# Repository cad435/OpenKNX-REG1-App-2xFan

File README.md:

# REG1-FanAktor-2x (V0.2)

Applikationsplatine (Addon-Board) für das [OpenKNX REG1](https://github.com/OpenKNX/OpenKNX-REG1) Modulsystem zur Ansteuerung von bis zu zwei Lüftern.

## Überblick

Die REG1-FanAktor-2x Platine wird zusammen mit dem [REG1-Controller2040](https://github.com/OpenKNX/OpenKNX-REG1/tree/main/hardware/EDA-Files/REG1-Controller2040) (RP2040-basiert) als Applikationsplatine in einem [REG1-Gehäuse](https://github.com/OpenKNX/OpenKNX/wiki/REG1-Case) (1TE, 17.5mm, DIN-Hutschiene) verbaut.

Die Platine steuert bis zu **2 unabhängige Lüfterausgänge** (Kanal A und B), jeweils mit:
- **PWM-Drehzahlregelung** (Open-Drain, 3.3V -> 5V über Level-Shifter)
- **Leistungsschalter** (High-Side-Switch für Ein/Aus)
- **Tacho-Eingang** (galvanisch isoliert über Optokoppler)

## Anschlüsse

### Lüfterklemmen

| Klemme | Bezeichnung | Funktion |
|--------|-------------|----------|
| **P1** | PWR IN | Lüfter-Versorgungsspannung (12...24V DC), 2-polig (FAN+, GND_FAN) |
| **P2** | FAN A | Lüfterausgang Kanal A, 4-polig (PWM_A_OUT, Tacho_A_IN, GND_FAN, GND_FAN) |
| **P3** | FAN B | Lüfterausgang Kanal B, 4-polig (PWM_B_OUT, Tacho_B_IN, GND_FAN, GND_FAN) |

Klemmentyp: KF2EDGR-3.5 (P1: 2-polig, P2/P3: 4-polig), Rastermaß 3.5mm.

### Controller-Schnittstelle

| Anschluss | Funktion |
|-----------|----------|
| **J1** | Header 1x10, Verbindung zum REG1-Controller2040 (GPIO, Versorgung) |

#### J1 Pinbelegung (vom Controller)

| Pin | Signal | GPIO | Funktion |
|-----|--------|------|----------|
| 1 | 12V | -- | Versorgungsspannung vom Controller |
| 2 | 3V3 | -- | 3.3V Versorgung vom Controller |
| 3 | GND_KNX | -- | Masse |
| 4 | GPIO18 | GP18 | PWM Kanal A |
| 5 | GPIO27 | GP27 | Tacho Kanal A (Eingang) |
| 6 | GPIO28 | GP28 | PWM Kanal B |
| 7 | GPIO29 | GP29 | Power-Switch Kanal A |
| 8 | GPIO26 | GP26 | Power-Switch Kanal B |
| 9 | GPIO17 | GP17 | Tacho Kanal B (Eingang) |
| 10 | GPIO16 | GP16 | Spare (auf J1 herausgeführt, nicht belegt) |

## Schaltungsbeschreibung

### Spannungsversorgung

Die Lüfter werden extern mit 12...24V DC über P1 versorgt.

### PWM-Ausgänge (Kanal A/B)

Jeder Kanal hat einen PWM-Ausgang zur Drehzahlregelung der Lüfter. Die Ausgänge sind galvanisch vom KNX-Bus getrennt ausgeführt.

### PWM Pull-Up Konfiguration (CN1...CN6)

Die Pull-Up-Konfiguration für die *PWM-Steuerung* wird über Lötbrücken eingestellt:

| Lüfter-Typ | Kanal A | Kanal B | Beschreibung |
|-------------|---------|---------|-------------|
| Interner Pull-Up vorhanden | Keine Brücke | Keine Brücke | Standardlüfter, keine externe Beschaltung nötig |
| Pull-Up auf 5V nötig | CN2 brücken | CN5 brücken | Pull-Up auf 5V |
| Pull-Up auf VCC (12-24V) nötig | CN1 brücken | CN4 brücken | Pull-Up auf Versorgungsspannung |
| Push-Pull Eingang | CN3 brücken, R1 entfernen | CN6 brücken, R3 entfernen | Für Lüfter mit Push-Pull-PWM-Eingang |

### ⚠️⚠️ Hinweis: ⚠️⚠️

Standard PC Lüfter und frei verkäufliche Typen haben zu 99% einen Integrierten Pullup. Standardmäßig ist keine der CNx Lötbrücken gesetzt, sodass diese Lüfter "out-of-the-box" funktionieren.

Bei Integrierten Anlagen (zum Beispiel dezentralen Lüftersystemen in der Gebäudetechnik) werden auch mal OEM-Varianten OHNE integrierte Pullups verbaut. Es empfiehlt sich ein genauer Blick auf die exakte Typennummer! Oftmals ist nur der Suffix ein Hinweis darauf. 

Von diesen Lüftern findet man in der Regel auch kein frei verfügbares Datenblatt. Hier muss man etwas Googlen welches die spezifische Referenzsspannung des jeweiligen Lüfterherstellers ist (bei ebm-Papst zum Beispiel meistens (!) 5V). Bei anderen Herstellern sind hier ggf. mit 3.3V oder anderem zu rechnen.

Eine Haftung für Schäden ist ausgeschlossen!

### Tacho-Eingänge

Jeder Kanal hat einen galvanisch getrennten Tacho-Eingang.

Typische Lüfter liefern 2 Pulse pro Umdrehung.

### Leistungsschalter (Power Ein/Aus)

Jeder Kanal hat einen High-Side-Switch zum An- und Ausschalten der Supply-Spannung für den Lüfter. Dies dient rein zur Eliminierung der Standbyleistung.

## Firmware

Die zugehörige Firmware basiert auf dem [OpenKNX](https://github.com/OpenKNX) Framework. Diese
Platine ist die **Referenz-Hardware** der Applikation — sie wird dort als primäre Variante
geführt und ist die einzige mit Tacho-Eingang:

- **OAM-FanControl**: [github.com/OpenKNX/OAM-FanControl](https://github.com/OpenKNX/OAM-FanControl/tree/cad435/main) (Branch `cad435/main`)
- **OFM-FanControl**: [github.com/OpenKNX/OFM-FanControl](https://github.com/OpenKNX/OFM-FanControl/tree/cad435/main) (Branch `cad435/main`)

Entwickelt wird in den Forks [cad435/OAM-FanControl](https://github.com/cad435/OAM-FanControl) und
[cad435/OFM-FanControl](https://github.com/cad435/OFM-FanControl) (Branch `main`).

Die Boardauswahl erfolgt zur Compile-Zeit, weil sich PWM-Polarität und Anzahl der Ausgänge
zwischen den Varianten unterscheiden. Für diese Platine ist das Environment
`develop_RP2040` zuständig.

> **Herkunft:** Ursprung der Applikation sind
> [mrspieb/OAM-FanControl](https://github.com/mrspieb/OAM-FanControl) und
> [mrspieb/OFM-FanControl](https://github.com/mrspieb/OFM-FanControl) für die
> [HW-FanControl](https://github.com/mrspieb/HW-FanController)-Platine. Die oben genannten
> Repositories sind Forks davon und inzwischen neu aufgebaut: Master/Slave-Gruppenbetrieb,
> reversierende Lüfter mit bipolarer Stellgröße auf einem Ausgang, Volumenstromkennlinie,
> Blockiererkennung. Das KO-Layout ist dadurch **nicht** mit der ursprünglichen Applikation
> kompatibel.

## Dateien

| Datei | Beschreibung |
|-------|-------------|
| `REG1-FanAktor-2x_V0.2-Schematic.PDF` | Schaltplan |
| `REG1-FanAktor-2x_V0.2-Pinout.PDF` | Pinbelegung und Lötbrücken-Konfiguration |
| `REG1-FanAktor-2x_V0.2_Assembly.PDF` | Bestückungsplan (Top/Bottom) |
| `BOM-REG1-FanAktor-2x(V0.2).pdf` | Stückliste |
| `JLC_PCBA_BOM-REG1-FanAktor-2x(V0.2).xlsx` | BOM für JLCPCB-Bestückung |
| `JLC_PCBA_CPL-REG1-FanAktor-2x(V0.2).xlsx` | Bauteilplatzierung für JLCPCB |
| `REG1-FanAktor-2x_Gerber.zip` | Gerber-Daten für PCB-Fertigung |
| `REG1-FanAktor-2x(V0.2).step` | 3D-Modell |

## Lizenz

Dieses Projekt ist Teil des [OpenKNX](https://github.com/OpenKNX) Ökosystems.

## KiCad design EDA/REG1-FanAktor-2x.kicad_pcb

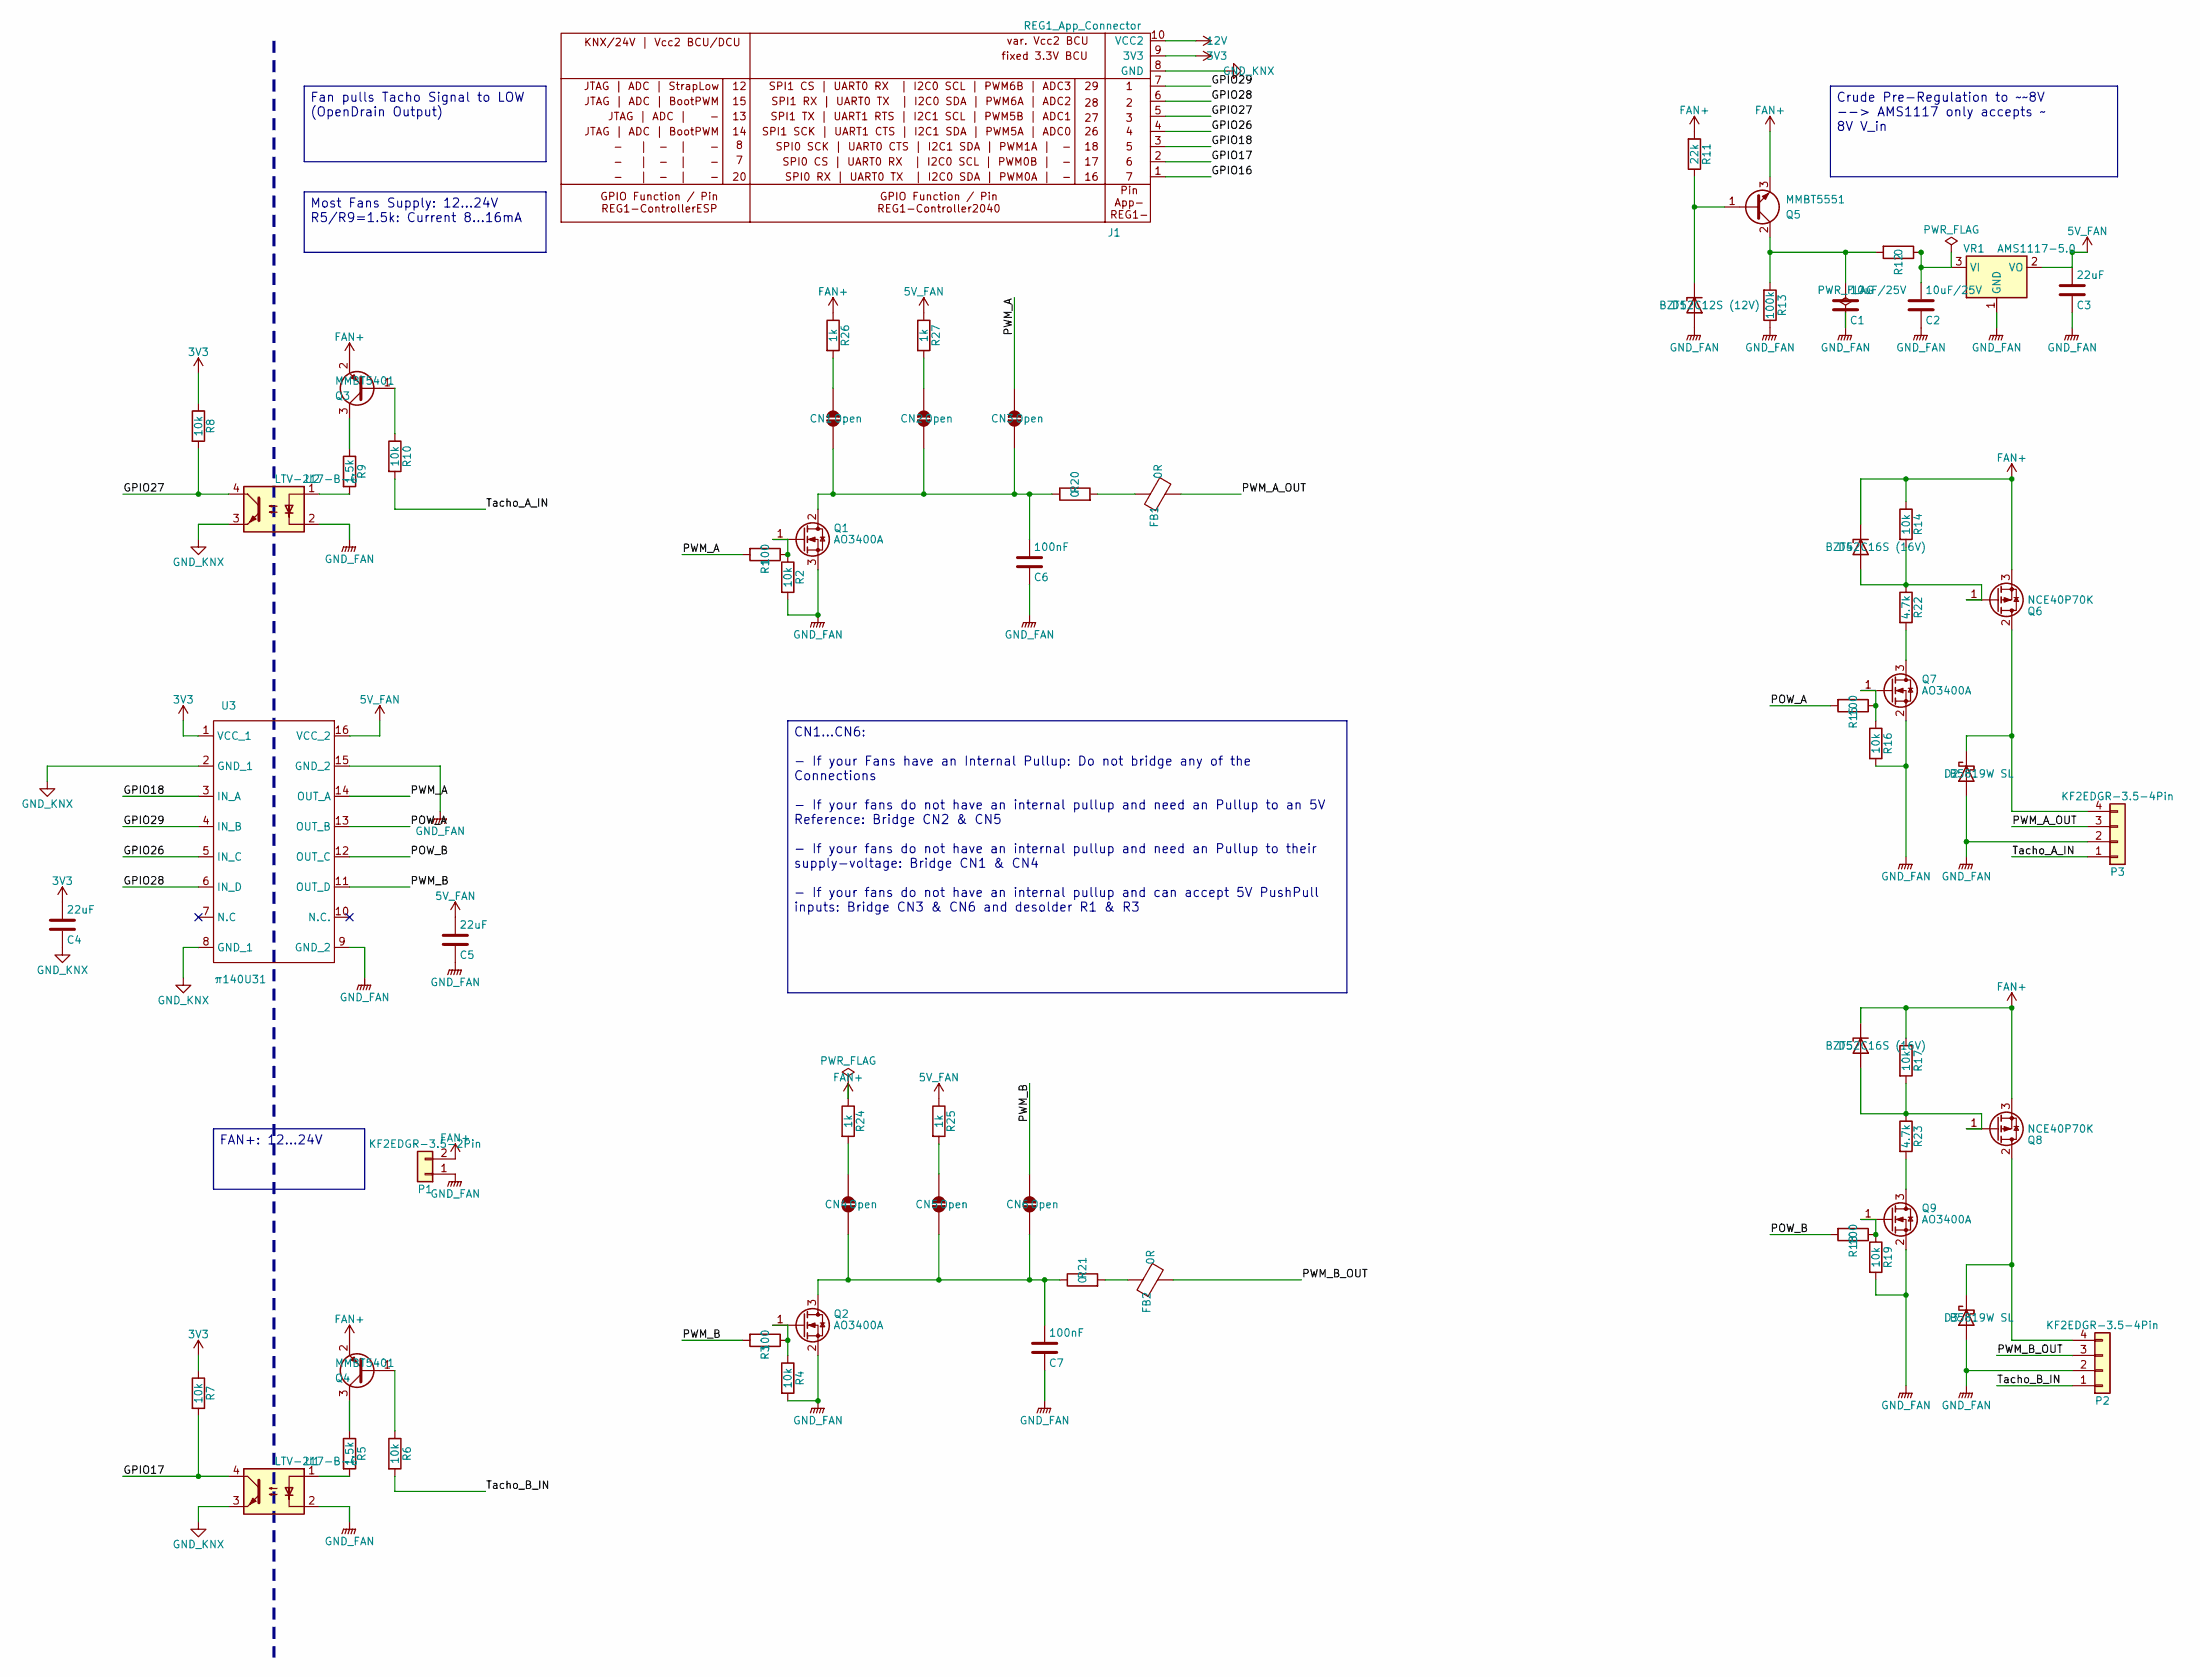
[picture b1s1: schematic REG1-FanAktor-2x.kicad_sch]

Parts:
C1, C2: 10uF/25V; C_0805_2012Metric; LCSC C440198
C3, C4, C5: 22uF; C_0805_2012Metric; LCSC C45783
C6, C7: 100nF; C_0603_1608Metric
CN1, CN2, CN3, CN4, CN5, CN6: Open; SB_0603
D1: BZT52C12S (12V); D_SOD-323; LCSC C19077447
D2, D3: B5819W SL; D_SOD-123; LCSC C8598
D4, D5: BZT52C16S (16V); D_SOD-323; LCSC C19077449
FB1, FB2: 0R; L_1206_3216Metric; LCSC C17888
J1: REG1_App_Connector; PinHeader_1x10_P2.54mm_Vertical
P1: KF2EDGR-3.5-2Pin; CONN-TH_2P-P3.50_KF2EDGR-3.5; LCSC C441171
P2, P3: KF2EDGR-3.5-4Pin; CONN-TH_4P-P3.50_KF2EDGR-3.5-4P
Q1: AO3400A; SOT23_Normal; LCSC C20917
Q2, Q7, Q9: AO3400A; SOT-23; LCSC C20917
Q3: MMBT5401; SOT-23; LCSC C8326
Q4: MMBT5401; SOT23_Reverse; LCSC C8326
Q5: MMBT5551; SOT-23; LCSC C2145
Q6, Q8: NCE40P70K; TO-252-2; LCSC C130101
R1, R3, R15, R18: 100; R_0603_1608Metric; LCSC C22775
R2, R4, R6, R7, R8, R10, R14, R16, R17, R19: 10k; R_0603_1608Metric; LCSC C25804
R5, R9: 1.5k; R_0603_1608Metric; LCSC C22843
R11: 22k; R_0603_1608Metric; LCSC C31850
R12, R20, R21: 0; R_1206_3216Metric; LCSC C17888
R13: 100k; R_0603_1608Metric; LCSC C25803
R22, R23: 4.7k; R_1206_3216Metric; LCSC C17936
R24, R25, R26: 1k; R_0805_2012Metric; LCSC C17513
R27: 1k; R0805; LCSC C17513
U1, U2: LTV-217-B-G; SOP-4_4.4x2.6mm_P1.27mm; LCSC C115450
U3: π140U31; SOIC127P600X180-16N; LCSC C471601
VR1: AMS1117-5.0; SOT-223-3_TabPin2; LCSC C6187

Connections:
3V3: C4.2, J1.9 (3V3), R7.1, R8.1, U3.1 (VCC_1)
5V_FAN: C3.2, C5.2, R25.1, R27.1, U3.16 (VCC_2), VR1.2 (VO)
12V: J1.10 (VCC2)
/GPIO16: J1.1
/GPIO17: J1.2, R7.2, U1.4
/GPIO18: J1.3, U3.3 (IN_A)
/GPIO26: J1.4, U3.5 (IN_C)
/GPIO27: J1.5, R8.2, U2.4
/GPIO28: J1.6, U3.6 (IN_D)
/GPIO29: J1.7, U3.4 (IN_B)
/POW_A: R15.2, U3.13 (OUT_B)
/POW_B: R18.2, U3.12 (OUT_C)
/PWM_A: CN3.2 (B), R1.2, U3.14 (OUT_A)
/PWM_A_OUT: FB1.2, P3.3
/PWM_B: CN6.2 (B), R3.2, U3.11 (OUT_D)
/PWM_B_OUT: FB2.2, P2.3
/Tacho_A_IN: P3.1, R10.2
/Tacho_B_IN: P2.1, R6.2
FAN+: D4.1 (K), D5.1 (K), P1.2, Q3.2 (E), Q4.2 (E), Q5.3 (E), Q6.3 (S), Q8.3 (S), R11.2, R14.1, R17.1, R24.1, R26.1
GND_FAN: C1.1, C2.1, C3.1, C5.1, C6.1, C7.1, D1.2 (A), D2.2 (A), D3.2 (A), P1.1, P2.2, P3.2, Q1.3 (S), Q2.2 (S), Q7.2 (S), Q9.2 (S), R2.2, R4.2, R13.1, R16.2, R19.2, U1.2, U2.2, U3.9 (GND_2), U3.15 (GND_2), VR1.1 (GND)
GND_KNX: C4.1, J1.8 (GND), U1.3, U2.3, U3.2 (GND_1), U3.8 (GND_1)
unnamed: C6.2, CN1.1 (A), CN2.1 (A), CN3.1 (A), Q1.2 (D), R20.1
unnamed: CN1.2 (B), R26.2
unnamed: CN2.2 (B), R27.2
unnamed: C7.2, CN4.1 (A), CN5.1 (A), CN6.1 (A), Q2.3 (D), R21.1
unnamed: CN4.2 (B), R24.2
unnamed: CN5.2 (B), R25.2
unnamed: D1.1 (K), Q5.1 (B), R11.1
unnamed: D2.1 (K), P3.4, Q6.2 (D)
unnamed: D3.1 (K), P2.4, Q8.2 (D)
unnamed: D4.2 (A), Q6.1 (G), R14.2, R22.1
unnamed: D5.2 (A), Q8.1 (G), R17.2, R23.1
unnamed: FB1.1, R20.2
unnamed: FB2.1, R21.2
unnamed: Q1.1 (G), R1.1, R2.1
unnamed: Q2.1 (G), R3.1, R4.1
unnamed: Q3.1 (B), R10.1
unnamed: Q3.3 (C), R9.1
unnamed: Q4.1 (B), R6.1
unnamed: Q4.3 (C), R5.1
unnamed: C1.2, Q5.2 (C), R12.2, R13.2
unnamed: Q7.3 (D), R22.2
unnamed: Q7.1 (G), R15.1, R16.1
unnamed: Q9.3 (D), R23.2
unnamed: Q9.1 (G), R18.1, R19.1
unnamed: R5.2, U1.1
unnamed: R9.2, U2.1
unnamed: C2.2, R12.1, VR1.3 (VI)

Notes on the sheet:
FAN+: 12...24V
Crude Pre-Regulation to ~~8V --> AMS1117 only accepts ~ 8V V_in
Most Fans Supply: 12...24V R5/R9=1.5k: Current 8...16mA
Fan pulls Tacho Signal to LOW (OpenDrain Output)
CN1...CN6: - If your Fans have an Internal Pullup: Do not bridge any of the Connections - If your fans do not have an internal pullup and need an Pullup to an 5V Reference: Bridge CN2 & CN5 - If your fans do not have an internal pullup and need an Pullup to their supply-voltage: Bridge CN1 & CN4 - 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

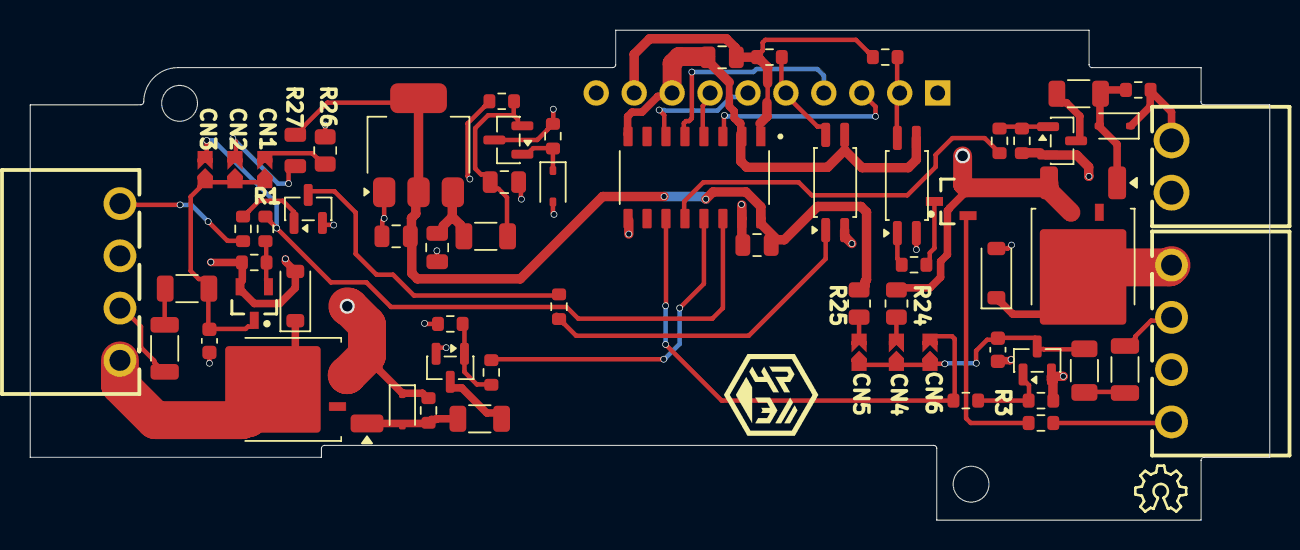
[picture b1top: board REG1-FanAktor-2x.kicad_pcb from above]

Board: 2 copper layers, 83.0 x 32.8 mm, 64 parts (1 on the bottom side), 46 nets.

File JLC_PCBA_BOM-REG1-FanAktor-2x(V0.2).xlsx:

Comment | Description | Value | Designator | Footprint | Quantity | JLCPCB Part #
10uF/25V | Capacitor | 100nF | C1, C2 | C0805 | 2 | C440198
22uF | Capacitor | 100nF | C3, C4, C5 | C0805 | 3 | C45783
Open | Circuit Breaker |  | CN4, CN5, CN6 | SB_0603 | 3
BZT52C12S (12V) | Zener |  | D1 | SOD-323 | 1 | C19077447
B5819W SL | Diode |  | D2, D3 | SOD-123 | 2 | C8598
BZT52C16S (16V) | Zener |  | D4, D5 | SOD-323 | 2 | C19077449
0R | Resistor | <no parameter> | FB1, FB2 | R1206 | 2 | C17888
Header 1x10 | Header 1x10 |  | J1 | Header 1x10 | 1
KF2EDGR-3.5-2Pin | KF2EDGR-3.5-2Pin |  | P1 | CONN-TH_2P-P3.50_KF2EDGR-3.5 | 1 | C441171
KF2EDGR-3.5-4Pin | KF2EDGR-3.5-4Pin |  | P2, P3 | CONN-TH_4P-P3.50_KF2EDGR-3.5-4P | 2
AO3400A | 30V N-Channel MOSFET |  | Q1, Q2, Q7, Q9 | SOT23 Normal | 4 | C20917
MMBT5401 | 60V, 600 mA, PNP switching transistor |  | Q3, Q4 | SOT23 Reverse | 2 | C8326
MMBT5551 | NPN General Purpose Transistor |  | Q5 | SOT23 Reverse | 1 | C2145
NCE40P70K | NCE P-Channel Enhancement Mode Power MOSFET |  | Q6, Q8 | TO-252 | 2 | C130101
100 | Resistor | 1.5k | R1, R3, R15, R18 | R0603 | 4 | C22775
10k | Resistor | 1.5k | R2, R4, R6, R7, R8, R10, R14, R16, R17, R19 | R0603 | 10 | C25804
1.5k | Resistor | 1.5k | R5, R9 | R0603 | 2 | C22843
22k | Resistor |  | R11 | R0603 | 1 | C31850
0 | Resistor |  | R12, R20, R21 | R1206 | 3 | C17888
100k | Resistor |  | R13 | R0603 | 1 | C25803
4.7k | Resistor | 1.5k | R22, R23 | R1206 | 2 | C17936
1k | Resistor | 1.5k | R24, R25, R26, R27 | R0805 | 4 | C17513
LTV-217-B-G | 4-Pin Phototransistor Optocoupler |  | U1, U2 | SOIC127P700X210-4N | 2 | C115450
π140U31 | Quad-Channel Digital Isolator |  | U3 | SOIC127P600X180-16N SOP-16 | 1 | C471601
AMS1117-5.0 | Voltage Regulator |  | VR1 | SOT223 | 1 | C6187
